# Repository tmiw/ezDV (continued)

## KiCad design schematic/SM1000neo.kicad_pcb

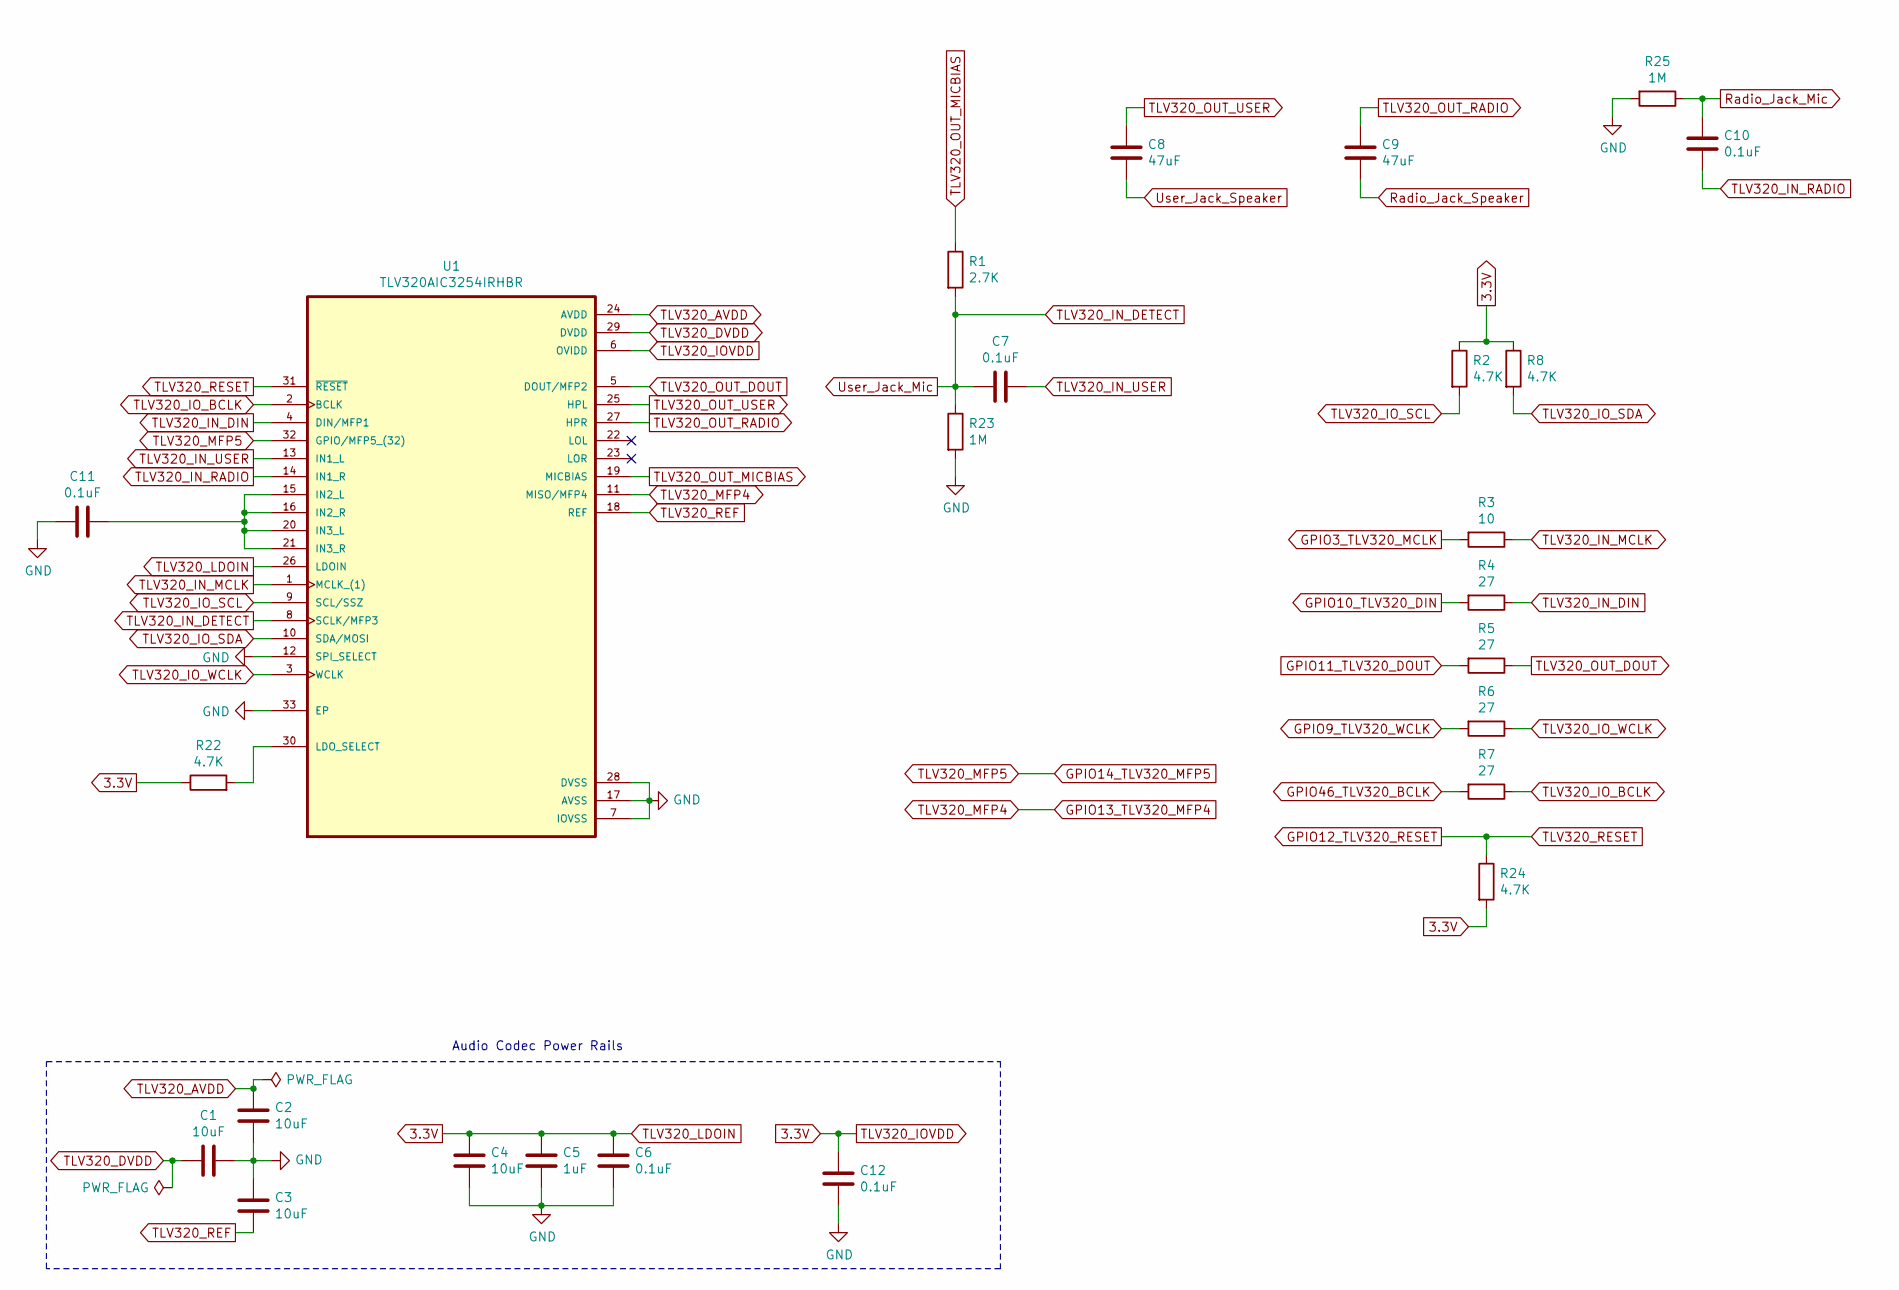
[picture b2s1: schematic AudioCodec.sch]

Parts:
C1, C2, C3, C4: 10uF; C_0402_1005Metric; LCSC C315248
C5: 1uF; C_0402_1005Metric; LCSC C14445
C6, C7, C10, C11, C12: 0.1uF; C_0402_1005Metric; LCSC C1525
C8, C9: 47uF; C_0603_1608Metric; LCSC C140782
R1: 2.7K; R_0603_1608Metric; LCSC C269437
R2, R8, R22, R24: 4.7K; R_0603_1608Metric; LCSC C99782
R3: 10; R_0603_1608Metric; LCSC C25202
R4, R5, R6, R7: 27; R_0603_1608Metric; LCSC C25190
R23, R25: 1M; R_0603_1608Metric; LCSC C22935
U1: TLV320AIC3254IRHBR; IC_ADS125H01IRHBT; LCSC C9925

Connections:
3.3V: C4.1, C5.1, C6.1, C12.1, R2.1, R8.1, R22.1, R24.2, U1.6 (OVIDD), U1.26 (LDOIN); also elsewhere on the board
GND: C1.1, C2.2, C3.1, C4.2, C5.2, C6.2, C11.2, C12.2, R23.2, R25.2, U1.7 (IOVSS), U1.12 (SPI_SELECT), U1.17 (AVSS), U1.28 (DVSS), U1.33 (EP), U1.34, U1.35, U1.36, U1.37, U1.38; also elsewhere on the board
GPIO3_TLV320_MCLK: R3.2; also elsewhere on the board
GPIO9_TLV320_WCLK: R6.2; also elsewhere on the board
GPIO10_TLV320_DIN: R4.2; also elsewhere on the board
GPIO11_TLV320_DOUT: R5.2; also elsewhere on the board
GPIO12_TLV320_RESET: R24.1, U1.31 (~RESET); also elsewhere on the board
GPIO13_TLV320_MFP4: U1.11 (MISO/MFP4); also elsewhere on the board
GPIO14_TLV320_MFP5: U1.32 (GPIO/MFP5_(32)); also elsewhere on the board
GPIO46_TLV320_BCLK: R7.2; also elsewhere on the board
GPIO47_TLV320_SDA: R8.2, U1.10 (SDA/MOSI); also elsewhere on the board
GPIO48_TLV320_SCL: R2.2, U1.9 (SCL/SSZ); also elsewhere on the board
unnamed: C11.1, U1.15 (IN2_L), U1.16 (IN2_R), U1.20 (IN3_L), U1.21 (IN3_R)
unnamed: R22.2, U1.30 (LDO_SELECT)
Radio_Jack_Mic: C10.1, R25.1; also elsewhere on the board
Radio_Jack_Speaker: C9.2; also elsewhere on the board
TLV320_AVDD: C2.1, U1.24 (AVDD)
TLV320_DVDD: C1.2, U1.29 (DVDD)
TLV320_IN_DETECT: C7.1, R1.2, R23.1, U1.8 (SCLK/MFP3); also elsewhere on the board
TLV320_IN_DIN: R4.1, U1.4 (DIN/MFP1)
TLV320_IN_MCLK: R3.1, U1.1 (MCLK_(1))
TLV320_IN_RADIO: C10.2, U1.14 (IN1_R)
TLV320_IN_USER: C7.2, U1.13 (IN1_L)
TLV320_IO_BCLK: R7.1, U1.2 (BCLK)
TLV320_IO_WCLK: R6.1, U1.3 (WCLK)
TLV320_OUT_DOUT: R5.1, U1.5 (DOUT/MFP2)
TLV320_OUT_MICBIAS: R1.1, U1.19 (MICBIAS)
TLV320_OUT_RADIO: C9.1, U1.27 (HPR)
TLV320_OUT_USER: C8.1, U1.25 (HPL)
TLV320_REF: C3.2, U1.18 (REF)
User_Jack_Speaker: C8.2; also elsewhere on the board

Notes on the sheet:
Audio Codec Power Rails

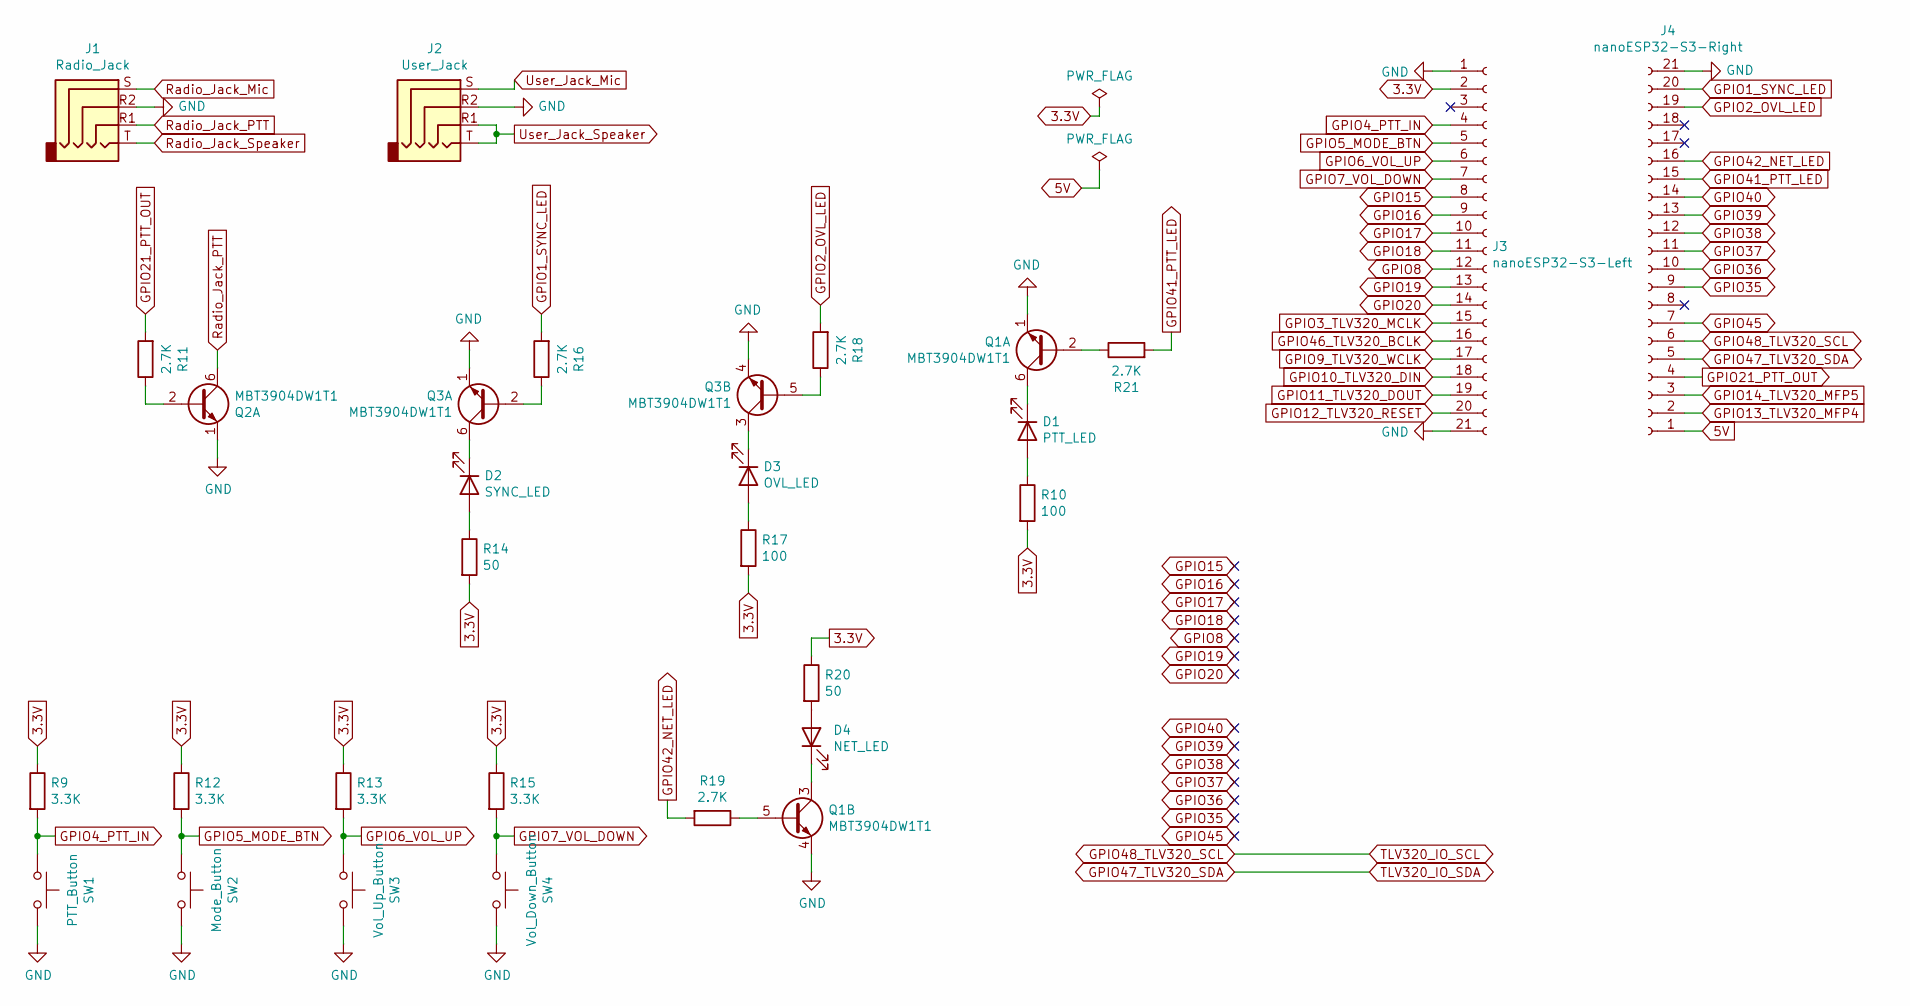
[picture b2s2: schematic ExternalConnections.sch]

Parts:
D1: PTT_LED; D_0603_1608Metric; LCSC C2286
D2: SYNC_LED; D_0603_1608Metric; LCSC C916073
D3: OVL_LED; D_0603_1608Metric; LCSC C2286
D4: NET_LED; D_0603_1608Metric; LCSC C193191
J1: Radio_Jack; Jack_3.5mm_PJ320D_Horizontal; LCSC C95562
J2: User_Jack; Jack_3.5mm_PJ320D_Horizontal; LCSC C95562
J3: nanoESP32-S3-Left; PinHeader_1x21_P2.54mm_Vertical
J4: nanoESP32-S3-Right; PinHeader_1x21_P2.54mm_Vertical
Q1, Q2, Q3: MBT3904DW1T1; SOT-363_SC-70-6; LCSC C110150
R9, R12, R13, R15: 3.3K; R_0603_1608Metric; LCSC C22978
R10, R17: 100; R_0603_1608Metric; LCSC C105588
R11, R16, R18, R19, R21: 2.7K; R_0603_1608Metric; LCSC C269437
R14, R20: 50; R_0603_1608Metric; LCSC C2759402
SW1: PTT_Button; SW_SPST_TL3342; LCSC C2886898
SW2: Mode_Button; SW_SPST_TL3342; LCSC C2886898
SW3: Vol_Up_Button; SW_SPST_TL3342; LCSC C2886898
SW4: Vol_Down_Button; SW_SPST_TL3342; LCSC C2886898

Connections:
3.3V: J3.2, R9.1, R10.2, R12.1, R13.1, R14.2, R15.1, R17.2, R20.1; also elsewhere on the board
5V: J4.1
GND: J1.R2, J2.R2, J3.1, J3.21, J4.21, Q1.1 (E1), Q1.4 (E2), Q2.1 (E1), Q3.1 (E1), Q3.4 (E2), SW1.2, SW2.2, SW3.2, SW4.2; also elsewhere on the board
GPIO1_SYNC_LED: J4.20, R16.2
GPIO2_OVL_LED: J4.19, R18.2
GPIO3_TLV320_MCLK: J3.15; also elsewhere on the board
GPIO4_PTT_IN: J3.4, R9.2, SW1.1
GPIO5_MODE_BTN: J3.5, R12.2, SW2.1
GPIO6_VOL_UP: J3.6, R13.2, SW3.1
GPIO7_VOL_DOWN: J3.7, R15.2, SW4.1
GPIO8: J3.12
GPIO9_TLV320_WCLK: J3.17; also elsewhere on the board
GPIO10_TLV320_DIN: J3.18; also elsewhere on the board
GPIO11_TLV320_DOUT: J3.19; also elsewhere on the board
GPIO12_TLV320_RESET: J3.20; also elsewhere on the board
GPIO13_TLV320_MFP4: J4.2; also elsewhere on the board
GPIO14_TLV320_MFP5: J4.3; also elsewhere on the board
GPIO15: J3.8
GPIO16: J3.9
GPIO17: J3.10
GPIO18: J3.11
GPIO19: J3.13
GPIO20: J3.14
GPIO21_PTT_OUT: J4.4, R11.2
GPIO35: J4.9
GPIO36: J4.10
GPIO37: J4.11
GPIO38: J4.12
GPIO39: J4.13
GPIO40: J4.14
GPIO41_PTT_LED: J4.15, R21.2
GPIO42_NET_LED: J4.16, R19.2
GPIO45: J4.7
GPIO46_TLV320_BCLK: J3.16; also elsewhere on the board
GPIO47_TLV320_SDA: J4.5; also elsewhere on the board
GPIO48_TLV320_SCL: J4.6; also elsewhere on the board
unnamed: D1.1 (K), Q1.6 (C1)
unnamed: D1.2 (A), R10.1
unnamed: D2.1 (K), Q3.6 (C1)
unnamed: D2.2 (A), R14.1
unnamed: D3.1 (K), Q3.3 (C2)
unnamed: D3.2 (A), R17.1
unnamed: D4.1 (K), Q1.3 (C2)
unnamed: D4.2 (A), R20.2
unnamed: Q1.2 (B1), R21.1
unnamed: Q1.5 (B2), R19.1
unnamed: Q2.2 (B1), R11.1
unnamed: Q3.2 (B1), R16.1
unnamed: Q3.5 (B2), R18.1
Radio_Jack_Mic: J1.S; also elsewhere on the board
Radio_Jack_PTT: J1.R1, Q2.6 (C1)
Radio_Jack_Speaker: J1.T; also elsewhere on the board
TLV320_IN_DETECT: J2.S; also elsewhere on the board
User_Jack_Speaker: J2.R1, J2.T; also elsewhere on the board

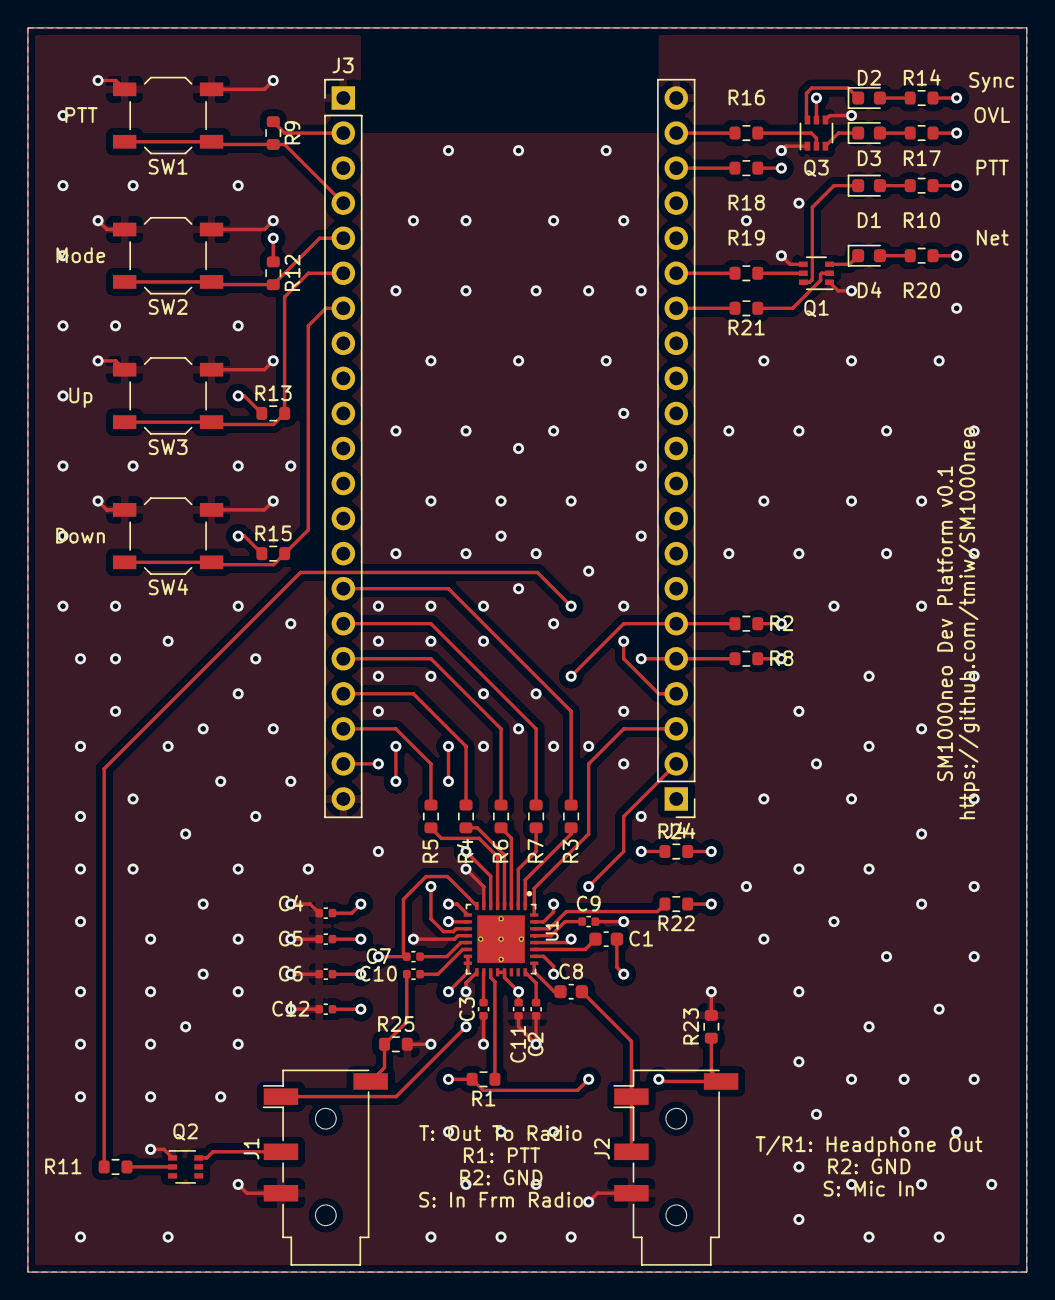
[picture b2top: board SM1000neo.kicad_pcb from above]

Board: 4 copper layers, 72.4 x 90.2 mm, 53 parts (0 on the bottom side), 54 nets.

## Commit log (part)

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2023-05-20 Undo change to allow 13 channels.
2023-06-03 Increase volume on receive as well.
2023-06-04 Add needed publish messages to have reporting work once implemented.
2023-06-25 Send received callsigns to FreeDV Reporter.
2023-06-26 Resolve TBD items for FreeDV Reporter implementation.
2023-06-28 Update AudioMixer to get rid of FPU usage.
2023-06-28 Ensure that we disconnect from FreeDV Reporter if we shut down SmartSDR.
2023-07-15 Fix bug preventing shutdown when Wi-Fi is not enabled.
2023-07-15 Get Flex support working again after previous changes.
2023-07-16 IC-705: add a bit more TX buffer for bad 2.4 GHz environments.
2023-07-17 Use slightly higher low battery threshold on startup.
    This allows ezDV to account for low battery shutdowns due to high
    current consumption and reduces the likelihood that the system will
    be allowed to start without first being at least partially recharged.
2023-07-30 Application config file changes due to updating ESP-IDF.
2023-08-05 Add an extra space to make the code easier to read.
2023-08-06 Use codec2-dev instead for now.
2023-08-25 Request current TX volume when IC-705 connection is starting up.
2023-08-25 Eliminate duplicate task callbacks when restarting after stop.
2023-08-25 Fix timing for test mode.
2023-08-27 Add more robust error handling for voice keyer updates.
2023-08-27 Fix bug preventing Flex radio drop-down from working properly if configuring from scratch.
2023-08-31 Add some delay when going back into receive to allow remaining output to be transmitted.
2023-08-31 Add ability to disable headset button.
2023-08-31 Remove obsolete/inaccurate comments.
2023-09-05 More changes to prevent words from cutting off at the end of transmissions:
    1. Add one frame of silence at the end of each transmission if a FreeDV mode is active.
    2. For IC-705, defer sending the CI-V command to release PTT until its own TX buffer is empty.
2023-09-07 Fix issue with FreeDV Reporter reporting incorrect frequency when using multiple slices on SmartSDR startup.
2023-09-10 Avoid duplicate wakeups from ULP.
2023-09-17 Shaved a few hundred milliseconds off of the boot time.
2023-09-17 Remove task affinity for Flex and FreeDV tasks to reduce dropouts.
2023-09-17 Enable ECC for external RAM.
2023-09-26 Don't blink the LEDs if the battery isn't actively charging.
2023-09-26 Add logic to make the buttons taller too.
2023-10-26 Fix bug causing crash when using ezDV as an AP.
2023-11-02 Add a bit more timeout in case the MAX17048 isn't there.
2023-11-11 Update issue templates
2023-11-12 Report OS to FreeDV Reporter.
2023-11-21 Fix crash when attempting to scan for networks in AP mode.
2023-11-23 Force stopping Wi-Fi scan if there are no more websockets connected.
2023-12-05 Send TransmitCompletedMessage on TX complete in analog mode as well.
2023-12-06 Hide radio username/password/port fields if Flex is chosen as the radio type.
2024-01-12 Clear any pending beeper message on shutdown to avoid crashes if shutting down too early.
2024-01-19 Go back to using ESP-IDF 5.1 stable.
2024-02-06 Refactor USB power detection so that it's more resilient to missed interrupts.
2024-02-08 Add v1.0 schematic.
2024-02-10 Use retry time limit instead of strict number of retries.
2024-02-10 Add glitch filter to GPIOs to prevent buttons from reading as being forced down on boot.
2024-02-10 Copy updated UDP retry logic to Flex driver.
2024-02-10 Suppress duplicate Wi-Fi entries from list sent over by ezDV.
2024-02-11 Reset PTT state on reconnection in case the user releases PTT before the latter.
2024-02-11 Only warn, don't request retransmit of missing RX packets.
2024-02-11 Reset totalTime so we can actually time out.
2024-02-20 Change the default radio port to 50001.
2024-02-20 Rename radioMac to match informal coding standard.
2024-02-20 Clean up compiler warnings for Wi-Fi initialization.
2024-02-20 Use official Codec2 instead of codec2-dev.
2024-02-20 Clean up warnings from the HTTP server.
2024-03-08 Experiment: different AGC config for user channel.
2024-03-08 Disable timer profiling.
2024-03-13 Fix issue preventing connection to FreeDV Reporter immediately on boot.
2024-03-14 Have static file requests take place on HttpServerTask (not ESP-IDF HTTP task).
    This is so that ezDV can handle more than one HTTP request at a time, improving performance
    and reducing the incidence of connection hangs.
2024-03-15 Add reporting message functionlity to FreeDV Reporter implementation.
2024-03-16 Increase message wait timeouts when saving settings.
2024-03-16 Refactor logic to load default values from configuration.
2024-03-16 Initial work on manual auto-generation.
2024-03-16 Hopefully apt-get update will cause packages to actually install.
2024-03-16 Add logic to push to github.io.
2024-03-16 Git user identity should be set in the repo we're actually pushing.
2024-03-16 Generated user manual from Git commit 209e18b
2024-03-16 Generated user manual from Git commit 58b5065
    Former-commit-id: 826d2ef56741fde7c95bdfb2c568084ce8197b82
2024-03-16 Add initial IC-705 setup instructions with guided photos.
2024-03-16 Flesh out the Introduction section.
2024-03-16 Fix typos.
2024-03-16 Make images smaller to avoid issues with GitHub Pages.
    Former-commit-id: 8fb91b42abc7c03a5dab4324eb6258def3907495
2024-03-16 Remove unused images.
2024-03-16 Finish Setup section of manual.
    Former-commit-id: f5d3ff37f74274673d764a55773e544d43de3a0f
2024-03-16 Slight rewording and TBD removal.
    Former-commit-id: 2d82dffb6dc32aec33b6bc9ebe9b344c5b60dbc5
2024-03-16 Add additional TOC levels to manual.
    Former-commit-id: 3bb9f5f65bb7dc8ed9f75ac8f20e7dbbf906fa6e
2024-03-16 Generated user manual from Git commit 3bb9f5f
    Former-commit-id: e73bb9b5447e405cdfefe97f5878bc9fae7d1af8
2024-03-16 Fix syntax error.
2024-03-16 Only generate the user manual if the source files have changed.
2024-03-16 Test documentation edit to force generation.
2024-03-16 Generated user manual from Git commit 1f1607a
2024-03-16 Add logic to create release when tagged.
2024-03-16 Fix incorrect paths.
2024-03-17 Fix typo in CSS classes used in the web interface.
2024-03-17 Fix trace messages in async static file handler.
2024-03-17 Reduce the amount of DRAM used by ezDV to hopefully avoid intermittent heap exhaustion.
2024-03-17 Move specific information about radio configuration to appendices.
2024-03-17 Forgot empty line between appendices.
2024-03-17 Flesh out Basic Operation section a bit more.
2024-03-17 Add FreeDV Reporter configuration/usage info.
2024-03-17 Generated user manual from Git commit 61e5106
2024-03-17 Fix typo in image URLs.
2024-03-17 Clean up README file since most content is now in the manual.
2024-03-18 Fix issues related to FreeDV Reporter not auto-reconnecting.
2024-03-18 Add PR template.
2024-03-18 Fix additional typos.
2024-03-19 Force VITA task and sample rate conversion to be compiled with optimization.
2024-03-19 Oops, FlexVitaTask lost its core affinity.
2024-03-19 Force TCP/IP and Wi-Fi tasks to core 1.
2024-03-19 Shave a few more KB from DRAM in the Icom code.
2024-03-19 Enable additional ESP-IDF Wi-Fi and TCP/IP related optimization options.
2024-03-20 Increase UDP RX mailbox size, causing most RX dropouts to stop happening on the Flex.
2024-03-20 Fix issue causing page to only half-reload after reboot.
2024-03-21 Add defer attribute to force specific load ordering for JS.
2024-03-21 Increase the maximum number of HTTP files and sockets that can be open.
2024-03-22 Determine the number of VITA packets to send based on the time since last call.
2024-03-22 Add algorithm to temporarily increase the minimum number of packets to send if the timing isn't quite right.
2024-03-22 Resync VITA TX if we run out of fifo.
2024-03-24 VoiceKeyerTask: queue up blocks of the VK file prior to sending for processing.
2024-03-24 Bump up stack and queue sizes based on crashes encountered.
2024-03-24 Improve algorithm to determine the number of packets to send.
    The Flex code now keeps a running total of how much extra time is required
    in between timer ticks. It then calculates the number of extra VITA packets
    required to be sent based on how many us we're behind what the radio expects,
    ensuring that the radio receives on average the correct number of packets
    in a given time interval.
2024-03-25 Update website icon to avoid confusion with FreeDV Reporter.
2024-03-25 Broadcast sync state every time through the loop (preventing stuck 'sync' LED issue).
2024-03-25 Reenable test code from earlier.
2024-03-26 Disable caching for all HTTP responses.
2024-03-26 Refactor DVTimer similarly as with DVTask.
    This change increases internal memory usage slightly but worth it for much better
    stack traces and the potential to reduce the stack allocation for certain tasks
    (getting back some of that used memory).
2024-03-26 Experiment: move event allocations to PSRAM.
2024-03-26 Fix issue where system crashes if FreeDV Reporter is connected and Wi-Fi suddenly goes down.
2024-03-27 Add debugging when the system crashes due to running out of queue space.
2024-03-28 Experiment: use khash library instead of STL for event registrations.
2024-03-30 Timers should be handled ASAP (another jitter reduction tactic).
2024-04-01 Reduce CPU time required by the VITA task.
2024-04-02 Have scaling happen while we're upsampling since we're already manipulating those samples anyway.
2024-04-04 Reduce per-loop instruction count in upsampling logic.
2024-04-04 Add additional documentation for debug flags.
2024-04-05 Add Kconfig options for various ezDV debugging output.
2024-04-05 Add additional help.
2024-04-06 VITA timestamps need to be in network order as well.
2024-04-07 Add support for Wi-Fi roaming.
2024-04-08 Only kill websocket task when ezDV is sleeping.
2024-04-08 Update esp_websocket_client to version 1.2.3.
2024-04-17 Remove remaining submodules.
2024-04-17 Remove ALL ezDV firmware code except absolute minimum needed for HTTP server.
2024-04-17 Re-enable async HTTP handling, causing crash.
2024-04-20 Create THEORY_OF_OPERATIONS.md
    Add Theory of Operations document describing the basic ezDV architecture. This should allow potential developers to get a handle on the system more quickly.
2024-04-20 Add additional info about message handling to the Theory of Ops.
2024-05-26 Use fixed-point multiplication for IC-705 audio output amplification.
2024-05-28 Change underlying mode for FreeDV LSB to DIGL
    The underlying mode should be DIGL for LSB similar to how it is DIGU
    for USB. This will disable any audio processing including CESSB and
    TX equalization that could corrupt the waveform.
2024-06-09 Add support for PSK Reporter to ezDV.
2024-06-10 Update documentation to reflect availability of PSK Reporter.
2024-06-11 Allow ezDV to boot without TLV320.
2024-06-11 Start HTTP server, etc. after Ethernet gets IP address.
2024-06-13 Make sure SNTP service starts when Ethernet comes up.
2024-06-13 Make sure Ethernet driver is uninitialized if we can't bring it up.
2024-06-13 Fix typo.
2024-06-27 Refactor network interface handling into separate classes.
2024-06-27 Make sure we only handle events that are supposed to be for us.
2024-06-27 Allow hostname to be set without enabling Wi-Fi first.
2024-07-04 Reporting: reset refcount to 0 on sleep to prevent stuck connections on waking.
2024-07-05 Override global operator new/delete to force all allocations onto SPIRAM.
2024-07-08 Update manual to reflect Ethernet support.
2024-07-21 Update minimum ESP-IDF to 5.2.2.
2024-07-24 Flex: fix issue preventing reconnection if there's a sudden power cut to the radio.
2024-07-26 Refactor I2C code to reflect preferred use of ESP-IDF's new I2C driver.
2024-07-26 Add System Status tab and display basic FreeDV stats.
2024-07-29 Update project to use ESP-IDF v5.3.
2024-07-29 Reenable async handling of static HTTP requests.
